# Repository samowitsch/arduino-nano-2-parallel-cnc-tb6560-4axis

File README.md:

# Arduino nano to parallel TB6560 cnc driver board adapter

This is my little Arduino nano to parallel TB6560 cnc driver board project. Started some time
ago using a red TB6560 4-axis board (before that i had an green 3-axis TB6560). 
At the moment the TB6560 alu case version is my preferred choice 
(but over time i can not remember why the red board was annoying me).
The adapter should also work with 3-axis TB6560 boards if the Pinout is the same.

* [KiCad](https://kicad.org/) files are included if you have special needs.
* Gerber files are included if you want to order your own pcb for e.g. at [jlcpcb.com](https://jlcpcb.com/)
* STL file of simple mount plate made with OpenSCAD is included if you have a 3d printer

Just work in progress current revision 1.4 using GRBL 1.1h.

## Known bugs of rev. 1.3

* holes for resistors are to close for "normal" resistors. my fault this is my first pcb project. i choose a wrong footprint.
* silk outline for X, Y, Z leds on pcb has wrong orientation (my fault or bug in KiCad library?)

## KiCad schema

## KiCad pcb wiring

## KiCad pcb 3d preview

## BOM for revision 1.4

Quantity | Pos | Part
--- | --- | ---
1 | | pcb from pcb manufacturer of your choice
1 | J1 | DSUB-25 female horizontal
5 | R1-R5 | 1k Ohm resistor
1 | Q1 | 2N3904 transistor
2 | SW1,SW2 | tactile push buttons 6x6
3 | D1-D3 | led 5mm
5 | J3,J4,J6,J8,J9 | jumper header 2 pins
3 | J2,J5,J7 | jumper header 3 pins
5 | | jumper
2 | | 15 pin single row female straight header strip 2.54mm pitch for arduino nano

## Simple mount in OpenSCAD

## Revision photos

Picture | Revision | Comment
--- | --- | ---
 | 1.0 | first dirty revision to get rid of the spaghetti grbl adapter ;o)
 | 1.1 | added jumper headers for the two versions (red pcb, alu case) of the TB6560
 | 1.2 | added two buttons for cycle start/resume and feed hold. added probe connector. added inverter circuit for spindle enable.
 | 1.3 | added leds just for fun.
No real pcb image yet | 1.4 | fix wrong orientation of leds. fix wrong footprint of resistors. reroute affected tracks.

## Pins

Arduino nano | GRBL 1.1 | DB25 red pcb | DB25 alu case version
---|---|---|---
D8 | Disable Stepper | 1 | 16
D2 | X Step | 2 | 2
D3 | Y Step | 4 (+8 A Step) | 4 (+8 A Step)
D4 | Z Step | 6 | 6
D5 | X Dir | 3 | 3
D6 | Y Dir | 5 (+9 A Dir) | 5 (+9 A Dir)
D7 | Z Dir | 7 | 7
D9 | X Limit | 10 (IN1) | 10 (IN1)
D10 | Y Limit | 11 (IN2) | 11 (IN2)
D11 | Spindle Enable | 14 | 17 (see PWM invert!)
D12 | Z Limit | 12 (IN3) | 12 (IN3)
D13 | Spindle Dir | 	 | 
A0 | Reset/Abort | 	 | 
A1 | Feed/Hold | 	 | 
A2 | Cycle Start/Resume | 	 | 
A3 | Cooling Enable | 	 | 
GND | GND | 18-25 | 18-25

## Jumper on board

There are some jumpers to configure the board for the two used 4-axis board versions.

Jumper | Description
---|---
J2 | connect Disable Stepper to pin 1* or pin 16** 
J3 | connect Y Step pin 4 to A Step pin 8
J4 | connect Y Dir pin 5 to A Dir pin 9
J5 | connect Spindle PWM to pin 14* or pin 17**
J6 | Probe connector
J7 | use PWM, inverted PWM or disable (no jumper) 
J8 | connector for alternative feed hold button
J9 | connector for alternative cycle start/resume button

*red board version / **alu case version

## PWM invert

TB6560 boards use low as spindle enable and high as spindel disable (WTF!?). It is the opposite way of how GRBL handle spindle enable/PWM.
The used invert circuit will fix this. But there is a little gap where the invert is not active during startup/shutdown.
> !!! As a workaround for now -> power on arduino at first and power off at last again to prevent injury through spindle.

Sources: 
* [How to setup inverting PWM signal and using +5v to switch off spindle motor? · Issue #22 · gnea/grbl · GitHub](https://github.com/gnea/grbl/issues/22)
* [GRBL PWM inverter circuit](https://blog.eccentricworkshop.com/grbl-pwm-inverter-circuit/)
* [Explain the Logic NOT Gate or Inverter and its Operation with Truth Table](https://electronicspost.com/explain-the-logic-not-gate-or-inverter-and-its-operation-with-truth-table/)

## My current GRBL settings

```
$$
$0=10
$1=25
$2=0
$3=5
$4=0
$5=0
$6=0
$10=1
$11=0.010
$12=0.002
$13=0
$20=0
$21=0
$22=0
$23=0
$24=25.000
$25=500.000
$26=250
$27=1.000
$30=1000
$31=0
$32=0
$100=402.000
$101=402.000
$102=402.000
$110=1500.000
$111=1500.000
$112=750.000
$120=42.000
$121=42.000
$122=42.000
$130=2000.000
$131=2000.000
$132=2000.000
```

## Probe G Codes

```
G38.2 z-10 f1
```
http://www.linuxcnc.org/docs/2.6/html/gcode/gcode.html#sec:G38-probe
```
G92 z19.2
```
http://www.linuxcnc.org/docs/2.6/html/gcode/gcode.html#sec:G92

## bCNC custom user button

Evaluate gcodes to test with bCNC custom user button.

```text
G38.2 z-100 f5 
G92 z19.7
G0 z50 f600
```

## Compiling GRBL

Download, extract and copy GRBL to the Arduino library. More details see here: https://github.com/gnea/grbl/wiki/Compiling-Grbl

Arduino IDE settings:
* Tools -> Board -> "Arduino Nano"
* Tools -> Processor -> "ATmega328P (Old Bootloader)"
* Tools -> Port -> "/dev/ttyUSB0" (may vary)
* Tools -> Programer -> "Atmel-ICE(AVR)"

## Arduino nano pinout

GRBL PWM enabled | GRBL
---|---
 | 

### Only for comparison GRBL on STM32F103C8T6 (bluepill)

Just for info. Interesting board with much faster cpu and more memory.  https://github.com/usbcnc/grbl

## other Source
* [Des Fricklers Fräse](https://der-frickler.net/technik/frickelfraese)
* [Make: China-Schrittmotorsteuerung](https://www.heise.de/make/artikel/3-Achs-Schrittmotorsteuerung-aus-China-1518901.html)
* [Grbl CNC USB to TB6560 Interface using Arduino](https://www.coreforge.com/blog/2014/08/grbl-tb6560-interface/)
* [G25 CNC Shield ](http://kclinear.com/G25/Instructions.pdf)

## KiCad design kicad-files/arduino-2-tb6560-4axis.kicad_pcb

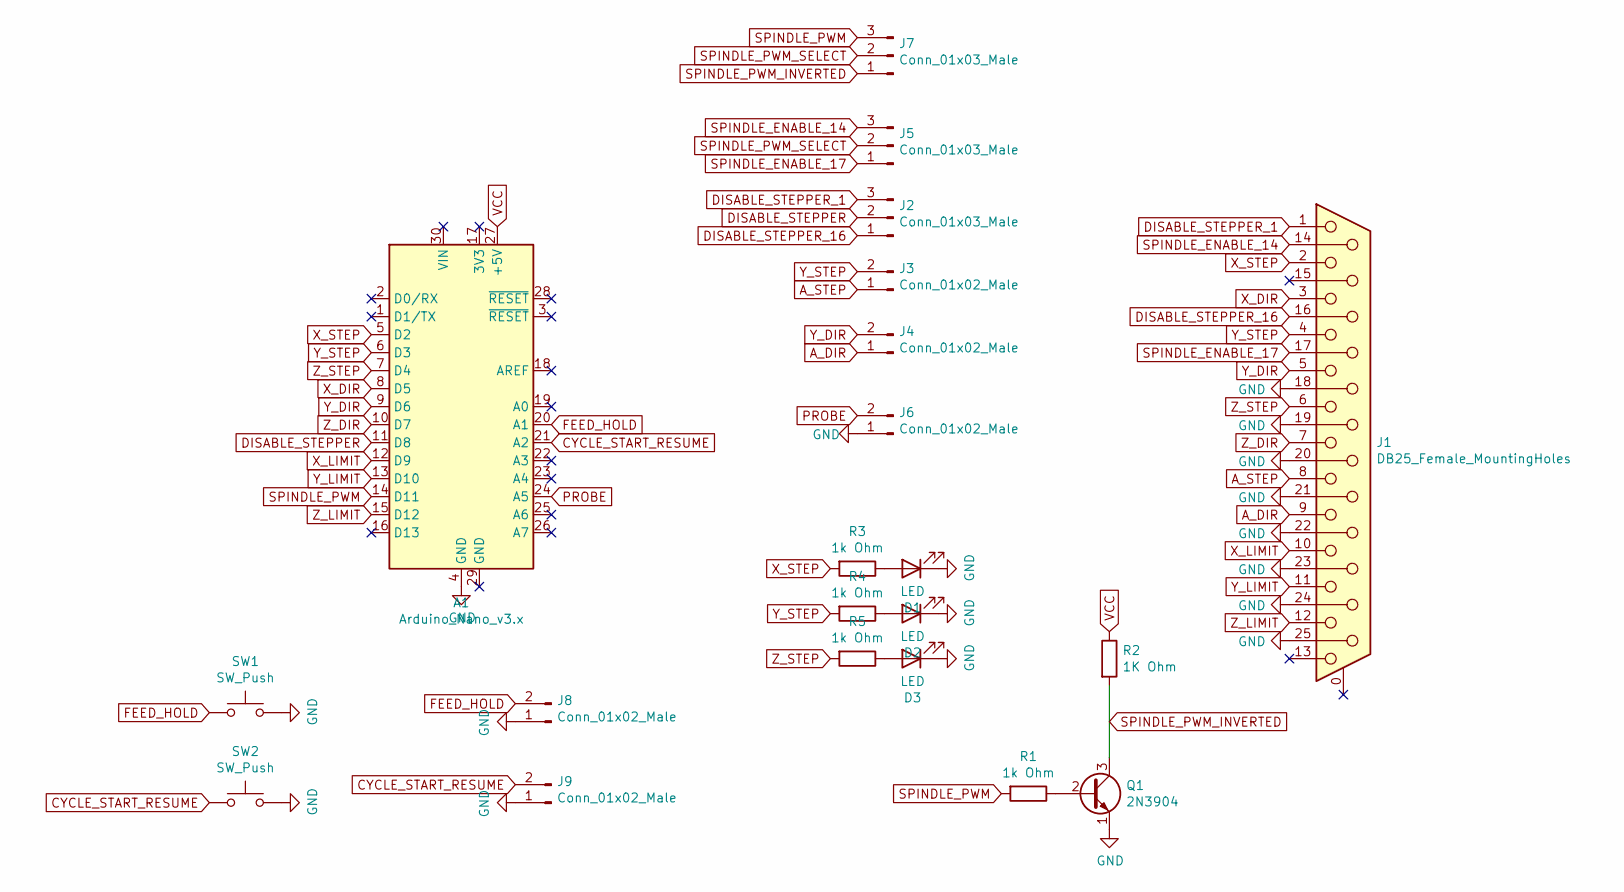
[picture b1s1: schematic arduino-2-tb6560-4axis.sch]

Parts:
A1: Arduino_Nano_v3.x; Arduino_Nano
D1, D2, D3: LED; LED_D5.0mm
J1: DB25_Female_MountingHoles; DSUB-25_Female_Horizontal_P2.77x2.54mm_EdgePinOffset9.40mm
J2, J5, J7: Conn_01x03_Male; PinHeader_1x03_P2.54mm_Vertical
J3, J4, J6, J8, J9: Conn_01x02_Male; PinHeader_1x02_P2.54mm_Vertical
Q1: 2N3904; TO-92_Inline
R1, R3, R4, R5: 1k Ohm; R_Axial_DIN0207_L6.3mm_D2.5mm_P7.62mm_Horizontal
R2: 1K Ohm; R_Axial_DIN0207_L6.3mm_D2.5mm_P7.62mm_Horizontal
SW1, SW2: SW_Push; SW_PUSH_6mm_H7.3mm

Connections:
A_DIR: J1.9, J4.1
A_STEP: J1.8, J3.1
CYCLE_START_RESUME: A1.21 (A2), J9.2, SW2.1
DISABLE_STEPPER: A1.11 (D8), J2.2
DISABLE_STEPPER_1: J1.1, J2.3
DISABLE_STEPPER_16: J1.16, J2.1
FEED_HOLD: A1.20 (A1), J8.2, SW1.1
GND: A1.4 (GND), D1.1 (K), D2.1 (K), D3.1 (K), J1.18, J1.19, J1.20, J1.21, J1.22, J1.23, J1.24, J1.25, J6.1, J8.1, J9.1, Q1.1 (E), SW1.2, SW2.2
unnamed: D1.2 (A), R3.1
unnamed: D2.2 (A), R4.1
unnamed: D3.2 (A), R5.1
unnamed: Q1.2 (B), R1.1
PROBE: A1.24 (A5), J6.2
SPINDLE_ENABLE_14: J1.14, J5.3
SPINDLE_ENABLE_17: J1.17, J5.1
SPINDLE_PWM: A1.14 (D11), J7.3, R1.2
SPINDLE_PWM_INVERTED: J7.1, Q1.3 (C), R2.2
SPINDLE_PWM_SELECT: J5.2, J7.2
VCC: A1.27 (+5V), R2.1
X_DIR: A1.8 (D5), J1.3
X_LIMIT: A1.12 (D9), J1.10
X_STEP: A1.5 (D2), J1.2, R3.2
Y_DIR: A1.9 (D6), J1.5, J4.2
Y_LIMIT: A1.13 (D10), J1.11
Y_STEP: A1.6 (D3), J1.4, J3.2, R4.2
Z_DIR: A1.10 (D7), J1.7
Z_LIMIT: A1.15 (D12), J1.12
Z_STEP: A1.7 (D4), J1.6, R5.2

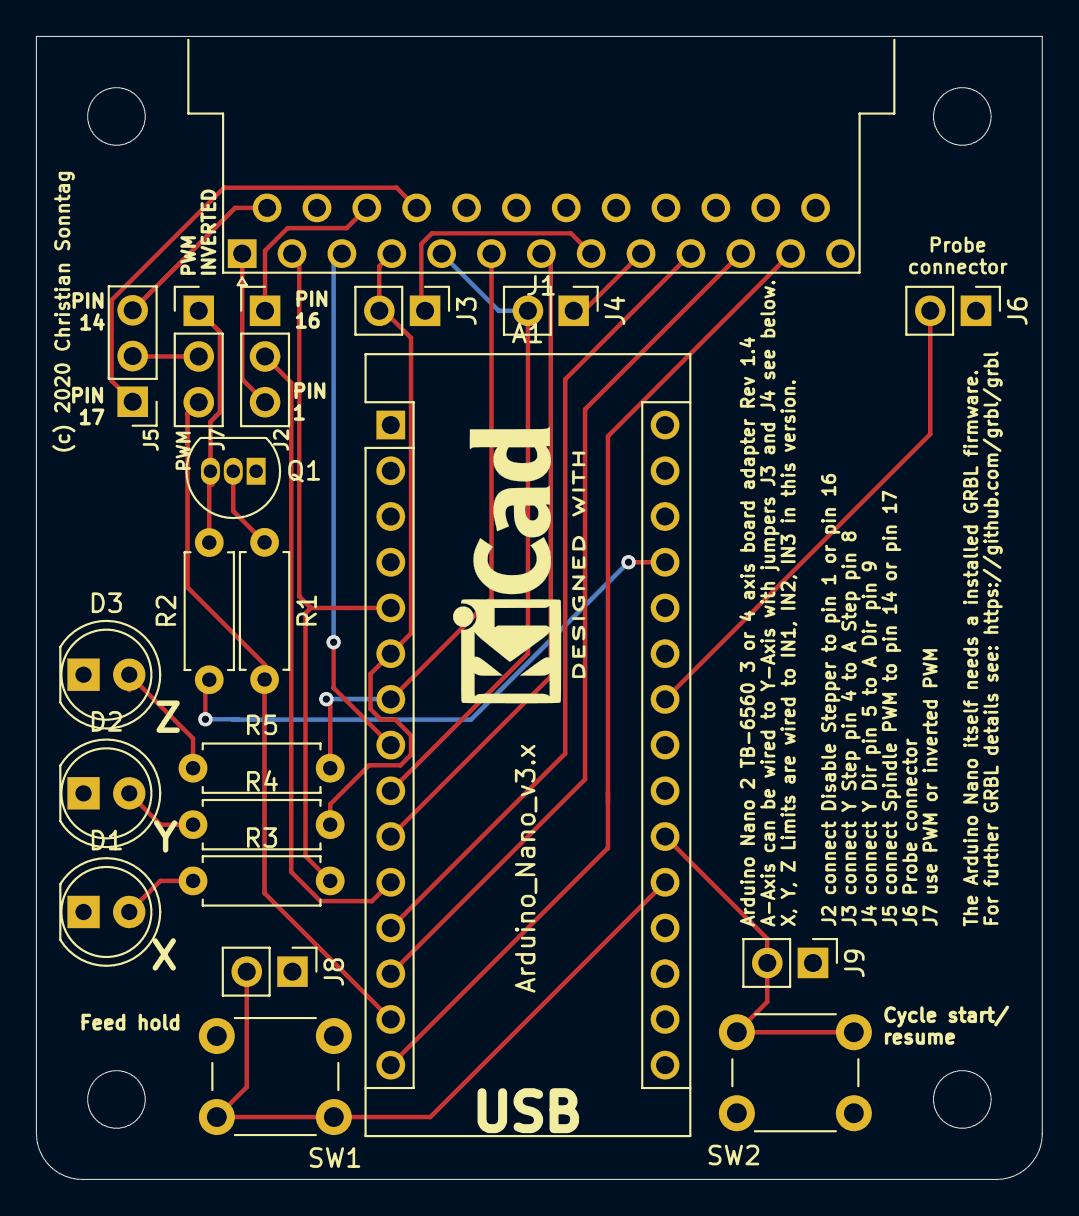
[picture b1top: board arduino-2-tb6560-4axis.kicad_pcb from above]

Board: 2 copper layers, 55.9 x 63.5 mm, 21 parts (0 on the bottom side), 28 nets.

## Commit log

2020-09-09 Update .gitignore, README.md, and 97 more files...
2020-09-11 added push buttons and jumper header for feed hold and cycle start/resume.
2020-09-11 updated images
2020-09-12 more ideas for rev 1.3
2020-09-19 changed readme. added simple mount created with OpenSCAD.
2020-09-19 misc
2020-09-24 added photo of rev 1.3. readme changes.
2020-09-24 readme changes
2020-09-26 added pcb pictures. add note for bCNC custom user button for probing. added some pdfs.
2020-09-26 fix wording
2020-09-27 add BOM
2020-09-27 rev. 1.4. fix wrong led orientation. fix wrong resistor footprint. reroute affected tracks.
2020-09-27 fix version number
2021-11-10 Update README.md
    https://forum.kicad.info/t/warning-avoid-all-links-to-kicad-pcb-org-use-kicad-org/31521
2023-09-18 add pdf doc about decay modes
2023-09-18 add GRBL 1.1 configuartion doc
2023-09-18 add GRBL 1.1 commands doc
2025-05-04 Add pdf

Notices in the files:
kicad-files/arduino-2-tb6560-4axis.kicad_pcb:
(c) 2020 Christian Sonntag
